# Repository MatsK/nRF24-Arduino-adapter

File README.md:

nRF24-Arduino-adapter
=====================

The goal is to create printed circuit boards for nRF24L01 modules that fits directly on different Arduino models and Raspberry Pi.

Boards
------
nRF24L01 - Arduino UNO
nRF24L01 - Arduino Nano
nRF24L01 - Arduino Mini Pro

Arduino with adapter and a nRF24L01 module

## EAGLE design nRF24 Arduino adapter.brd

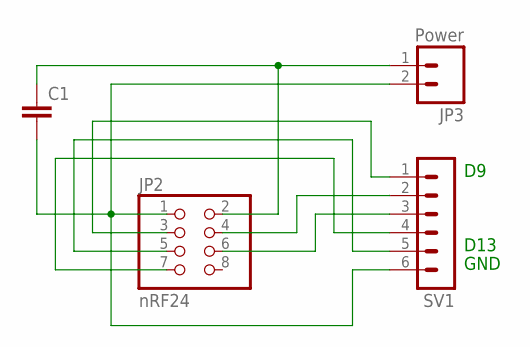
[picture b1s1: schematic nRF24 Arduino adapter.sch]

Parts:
C1: C2,5-3; C2.5-3
JP2: nRF24; 2X04
JP3: Power; 1X02_LOCK_LONGPADS
SV1: MA06-1

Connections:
unnamed: C1.2, JP2.1, JP3.2, SV1.6
unnamed: JP2.3, SV1.1
unnamed: C1.1, JP2.2, JP3.1
unnamed: JP2.4, SV1.2
unnamed: JP2.6, SV1.3
unnamed: JP2.5, SV1.5
unnamed: JP2.7, SV1.4

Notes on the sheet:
D13
GND

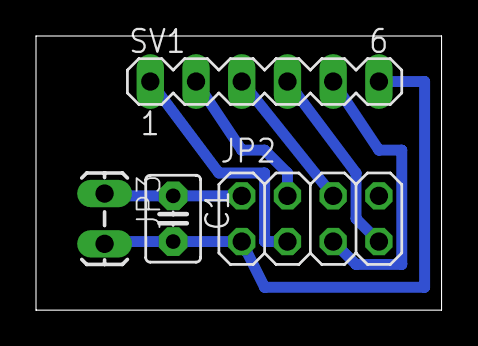
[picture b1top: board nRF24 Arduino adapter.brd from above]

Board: 2 copper layers, 22.5 x 15.2 mm, 4 parts (0 on the bottom side), 7 nets.

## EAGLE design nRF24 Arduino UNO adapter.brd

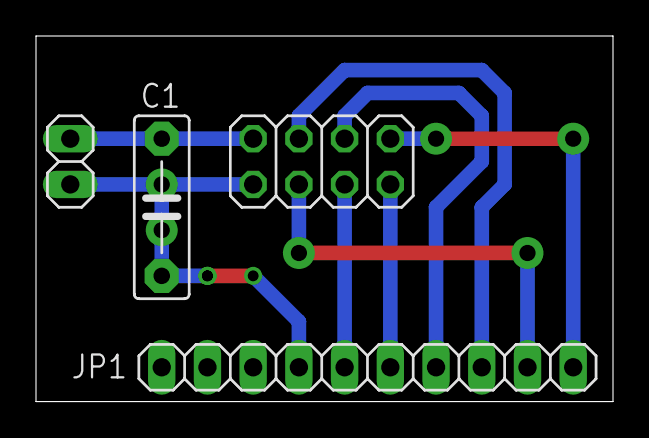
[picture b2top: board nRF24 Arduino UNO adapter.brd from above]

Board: 2 copper layers, 32.1 x 20.3 mm, 4 parts (0 on the bottom side), 8 nets.

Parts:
C1: 100n; C7.5B3
JP1: 1X10
JP2: nRF24; 2X04
JP3: 1X02

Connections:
+3V3: C1.1, JP2.2, JP3.1
CE: JP1.2, JP2.3
CSN: JP1.3, JP2.4
GND: C1.2, JP1.7, JP2.1, JP3.2
IRQ: JP1.1, JP2.8
MISO: JP1.5, JP2.7
MOSI: JP1.4, JP2.6
SCK: JP1.6, JP2.5

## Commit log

2014-07-04 First release
    First
2014-07-04 Create README.md
    First release
2014-07-04 Pictures
2014-07-04 Added picture to README.md
2014-07-04 link
2014-07-04 New pic
2014-07-04 small adjustments
2014-07-05 New version of schema
    Thanks to Rikard "Ornotermes" Lindström for the help
2014-07-05 Small changes
2014-07-05 added vcc

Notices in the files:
parts and their libraries:
SparkFun-Connectors: Licensing: Creative Commons ShareAlike 4.0 International - https://creativecommons.org/licenses/by-sa/4.0
